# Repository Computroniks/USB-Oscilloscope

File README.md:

<!-- 
SPDX-FileCopyrightText: 2022 Matthew Nickson <mnickson@sidingsmedia.com>
SPDX-License-Identifier: CC-BY-SA-4.0
-->

# USB-Oscilloscope

Simple USB Oscilloscope using ATTiny85

## Building

To build this project, you must have downloaded the AVR toolchain. You
can get the toolchain in a number of ways. See
https://www.microchip.com/en-us/tools-resources/develop/microchip-studio/gcc-compilers
for toolchain downloads. The toolchain should also be added to path.

### Requirements

| Name | Version | Website |
|---|---|---|
| CMake | >= 3.23.0 | https://www.cmake.org |
| AVR Toolchain | >= 3.6.2 | https://www.microchip.com/en-us/tools-resources/develop/microchip-studio/gcc-compilers |

### CMake Parameters

Here are some important parameters than can be configured when running
CMake.

| Parameter | Value | Description |
|---|---|---|
| CMAKE_BUILD_TYPE | One of `Debug` or `Release` (default `Debug`) | Sets the build type for CMake|
| F_CPU | Integer (default `16000000UL`| Clock speed in MHz |
| MCU | String (default `attiny85`) | The MCU being used. |
| PROG_TYPE| String (default `usbtiny`)| ISP Programmer used by AVRDUDE. See `avrdude -c ?` for list of valid values |
| E_FUSE | Integer (default `0xFF`) | Value for extra fuse |
| H_FUSE | Integer (default `0xD9`) | Value for high fuse |
| L_FUSE | Integer (default `0xDF`) | Value for low fuse |
| LOCK_BIT | Integer (default `0xFF`) | Value for lock bit |
| BAUD | Integer (default `9600`) | Baud rate for programmer |

To set an option add `-D\<option>=\<value>` to the CMake command. E.g To
set the MCU use `-DMCU=attiny45`.

### Compiling

To compile you should run the following. Note: This assumes that you are
using the `Unix Makefiles` generator with CMake. If you are using
another generator like Ninja your commands may be diffrent.

```
mkdir build
cd build
cmake ..
make
```

To upload the compiled firmware to the board, ensure that your
programmer is correctly connected and then run:
```
make upload
```

To set the board fuses you should run:
```
make fuse
```

### Source lists
A list of all files that the compiler will compile is contained in
`cmake/sourcelist.cmake`. If a new file is added or an old one deleted,
this list must be updated.

## Licence
This project uses the [REUSE](https://reuse.software) standard in order
to communicate the correct licence for the file. For those unfamiliar
with the standard the licence for each file can be found in one of three
places. The licence will either be in a comment block at the top of the
file, in a `.license` file with the same name as the file, or in the
dep5 file located in the `.reuse` directory.

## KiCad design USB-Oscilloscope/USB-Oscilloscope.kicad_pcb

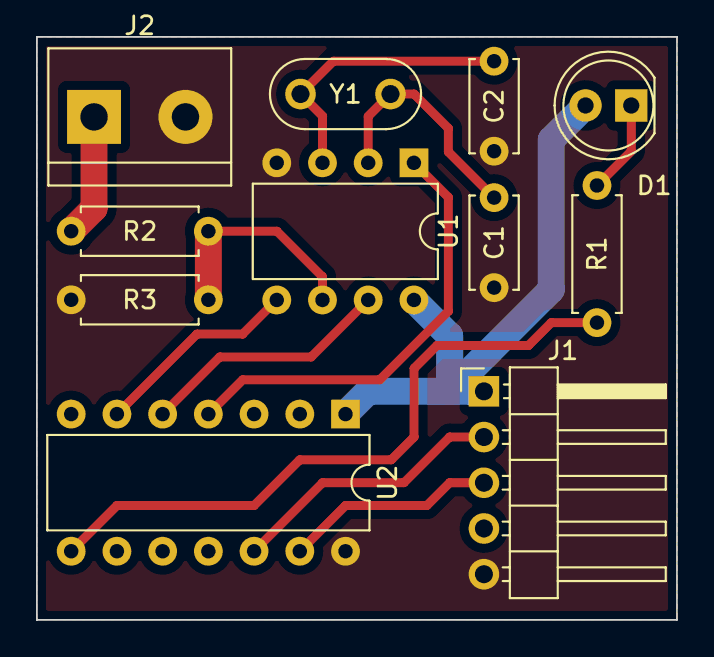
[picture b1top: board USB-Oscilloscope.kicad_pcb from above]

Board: 2 copper layers, 35.6 x 32.4 mm, 11 parts (0 on the bottom side), 13 nets.

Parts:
C1, C2: 27pF; C_Disc_D5.0mm_W2.5mm_P5.00mm
D1: LED; LED_D5.0mm
J1: USB_B_Micro; PinHeader_1x05_P2.54mm_Horizontal
J2: Screw_Terminal_01x02; TerminalBlock_bornier-2_P5.08mm
R1: 330; R_Axial_DIN0207_L6.3mm_D2.5mm_P7.62mm_Horizontal
R2: 100K; R_Axial_DIN0207_L6.3mm_D2.5mm_P7.62mm_Horizontal
R3: 10K; R_Axial_DIN0207_L6.3mm_D2.5mm_P7.62mm_Horizontal
U1: ATtiny85-20P; DIP-8_W7.62mm
U2: MCP2221AxP; DIP-14_W7.62mm
Y1: 16MHz; Resonator-2Pin_W8.0mm_H3.5mm

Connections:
+5V: D1.2 (A), J1.1 (VBUS), U1.8 (VCC), U2.1 (VDD)
/MCU_RXD: U1.5 (AREF/PB0), U2.6 (UTx)
/MCU_TXD: U1.7 (PB2), U2.5 (URx)
/SENSE: R2.2, R3.1, U1.6 (PB1)
/~RESET: U1.1 (~RESET/PB5), U2.4 (~RST)
GND: C1.1, C2.1, J1.5 (GND), J2.2, R3.2, U1.4 (GND), U2.14 (VSS)
unnamed: C1.2, U1.2 (XTAL1/PB3), Y1.2
unnamed: C2.2, U1.3 (XTAL2/PB4), Y1.1
unnamed: D1.1 (K), R1.1
unnamed: J1.2 (D-), U2.12 (D-)
unnamed: J1.3 (D+), U2.13 (D+)
unnamed: J2.1, R2.1
unnamed: R1.2, U2.8 (GP3)

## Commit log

2022-02-13 Basic project config
2022-02-13 Updated gitignore with backup files
2022-02-13 Rev 0.1 of Schematic and PCB
2022-02-13 Added MIT License
2022-02-13 Updated gitignore with compiler files
2022-02-13 Added style config
2022-02-15 Added basic build system
2022-02-15 Added documentation generator
